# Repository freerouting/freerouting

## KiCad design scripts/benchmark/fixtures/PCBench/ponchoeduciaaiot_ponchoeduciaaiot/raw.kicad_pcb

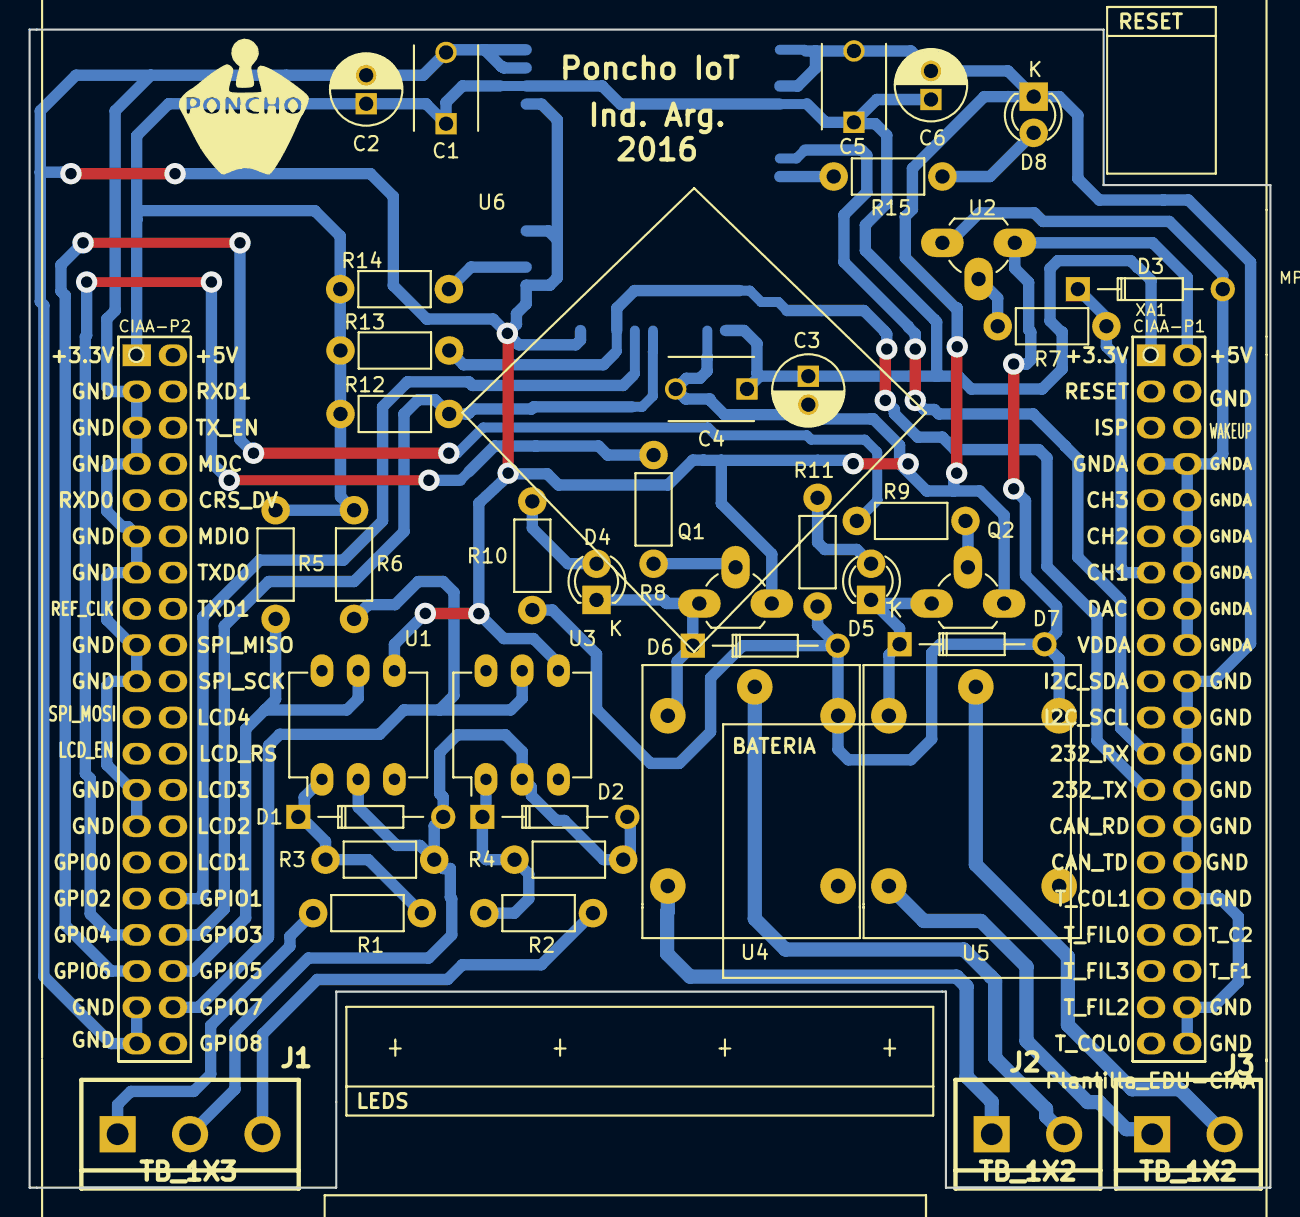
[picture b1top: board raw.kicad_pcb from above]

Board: 2 copper layers, 87.0 x 81.2 mm, 42 parts (0 on the bottom side), 32 nets.

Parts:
C1, C4, C5: 100nF; C_Disc_D6_P5
C2, C3, C6: 2.2uF; C_Radial_D5_L11_P2
D1, D2, D6, D7: 1N4007; Diode_DO-35_SOD27_Horizontal_RM10
D3: 1N4728A; Diode_DO-35_SOD27_Horizontal_RM10
D4, D5, D8: LED; LED-3MM
J1: TB_1X3; bornier3
J2, J3: TB_1X2; bornier2
MP?: Plantilla_EDU-CIAA
Q1, Q2: BC548; TO-92_Rugged
R1, R2: 3.3k; Resistor_Horizontal_RM7mm
R3, R4: 4.7k; Resistor_Horizontal_RM7mm
R5, R6, R8, R9, R12, R14: 10k; Resistor_Horizontal_RM7mm
R7, R15: 150; Resistor_Horizontal_RM7mm
R10, R11: 330; Resistor_Horizontal_RM7mm
R13: 100k; Resistor_Horizontal_RM7mm
U1, U3: 4N25; DIP-6_W7.62mm_LongPads
U2: LM35; TO-92_Rugged
U4, U5: RELAY; Relay5vSI
U6: RN1810E; RN1810
XA1: Conn_Poncho2P_2x_20x2; Conn_Poncho_Mediano

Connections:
+3V3: C1.1, C2.1, C3.1, C4.1, C5.1, C6.1, R5.1, R6.1, R12.1, R13.1, R14.1, U6.4, U6.15, U6.35, XA1.1, XA1.41
+5V: D6.2, D7.2, R10.1, R11.1, U2.1, U4.2, U5.2, XA1.2
/ConectoresPoncho/ANALOG_IN: D3.1, R7.1, XA1.13
/ConectoresPoncho/MODULE_RESET: R12.2, U6.19, XA1.74
/ConectoresPoncho/RXD_EDUCIAA: U6.7, XA1.23
/ConectoresPoncho/TXD_EDUCIAA: R13.2, U6.21, XA1.25
/comm/CMD_CTRL: U6.20, XA1.72
/gpios/IN0: R5.2, U1.5, XA1.76
/gpios/IN1: R6.2, U3.5, XA1.78
/gpios/OUT0: R8.2, XA1.73
/gpios/OUT1: R9.2, XA1.75
GND: C1.2, C2.2, C3.2, C4.2, C5.2, C6.2, D8.1, Q1.3, Q2.3, U1.4, U3.4, U6.1, U6.3, U6.16, U6.23, U6.24, U6.27, U6.34, U6.36, U6.37, XA1.20, XA1.22, XA1.24, XA1.26, XA1.28, XA1.30, XA1.32, XA1.38, XA1.40, XA1.43, XA1.45, XA1.47, XA1.51, XA1.53, XA1.57, XA1.59, XA1.65, XA1.67, XA1.77, XA1.79
GNDA: D3.2, U2.3, XA1.7, XA1.8, XA1.10, XA1.12, XA1.14, XA1.16, XA1.18
unnamed: D1.1, R1.1, R3.1, U1.1
unnamed: D1.2, D2.2, J1.2, R3.2, R4.2, U1.2, U3.2
unnamed: D2.1, R2.1, R4.1, U3.1
unnamed: D4.1, D6.1, Q1.1, U4.1
unnamed: D4.2, R10.2
unnamed: D5.1, D7.1, Q2.1, U5.1
unnamed: D5.2, R11.2
unnamed: D8.2, R15.1
unnamed: J1.1, R1.2
unnamed: J1.3, R2.2
unnamed: J2.1, U4.4
unnamed: J2.2, U4.3
unnamed: J3.1, U5.4
unnamed: J3.2, U5.3
unnamed: Q1.2, R8.1
unnamed: Q2.2, R9.1
unnamed: R7.2, U2.2
unnamed: R14.2, U6.25
unnamed: R15.2, U6.8

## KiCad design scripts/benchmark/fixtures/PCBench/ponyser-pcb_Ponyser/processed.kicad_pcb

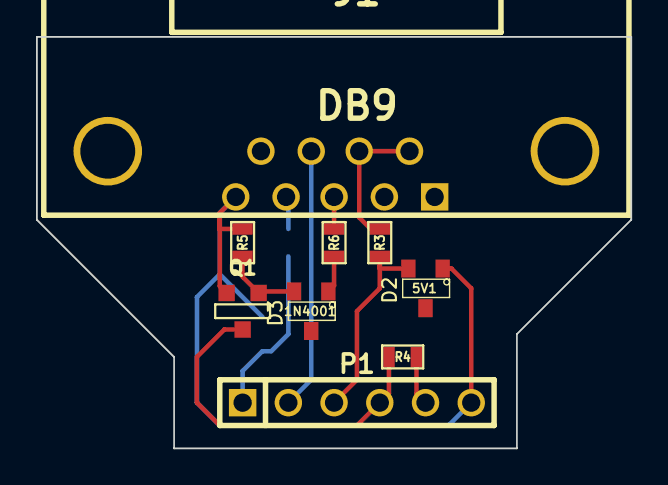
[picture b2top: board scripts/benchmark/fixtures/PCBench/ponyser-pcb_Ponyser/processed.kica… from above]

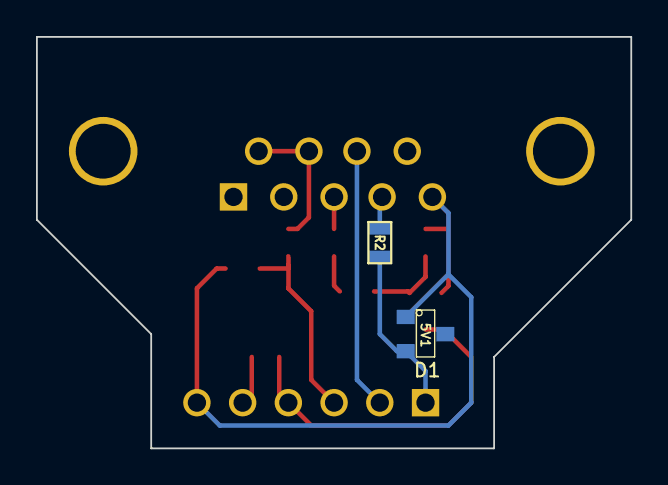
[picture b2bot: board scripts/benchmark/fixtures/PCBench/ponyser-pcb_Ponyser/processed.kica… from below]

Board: 2 copper layers, 33.0 x 22.9 mm, 12 parts (2 on the bottom side), 11 nets.

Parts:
D1, D2: 5V1; SOT23
D3: 1N4001; SOT23
J1: DB9; DB9MC
P1: CONN_6; PIN_ARRAY-6X1
Q1: NPN; SOT23EBC
R2, R3: 4k7; SM0603
R4, R6: 10k; SM0603
R5: 22k; SM0603
STUB: VAL**; STUB

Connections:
GND: D1.1, D2.1, J1.5, P1.6, Q1.1, R5.1
MISO: J1.8, P1.2
MOSI: D1.2, P1.1, R2.2
unnamed: D3.2, Q1.2, R5.2
unnamed: J1.4, R2.1
unnamed: J1.3, R6.1
unnamed: D3.1, R6.2
unnamed: J1.6, J1.7, R3.1
RESET: P1.4, Q1.3, R4.1
SCK: D2.2, P1.3, R3.2
VCC: P1.5, R4.2

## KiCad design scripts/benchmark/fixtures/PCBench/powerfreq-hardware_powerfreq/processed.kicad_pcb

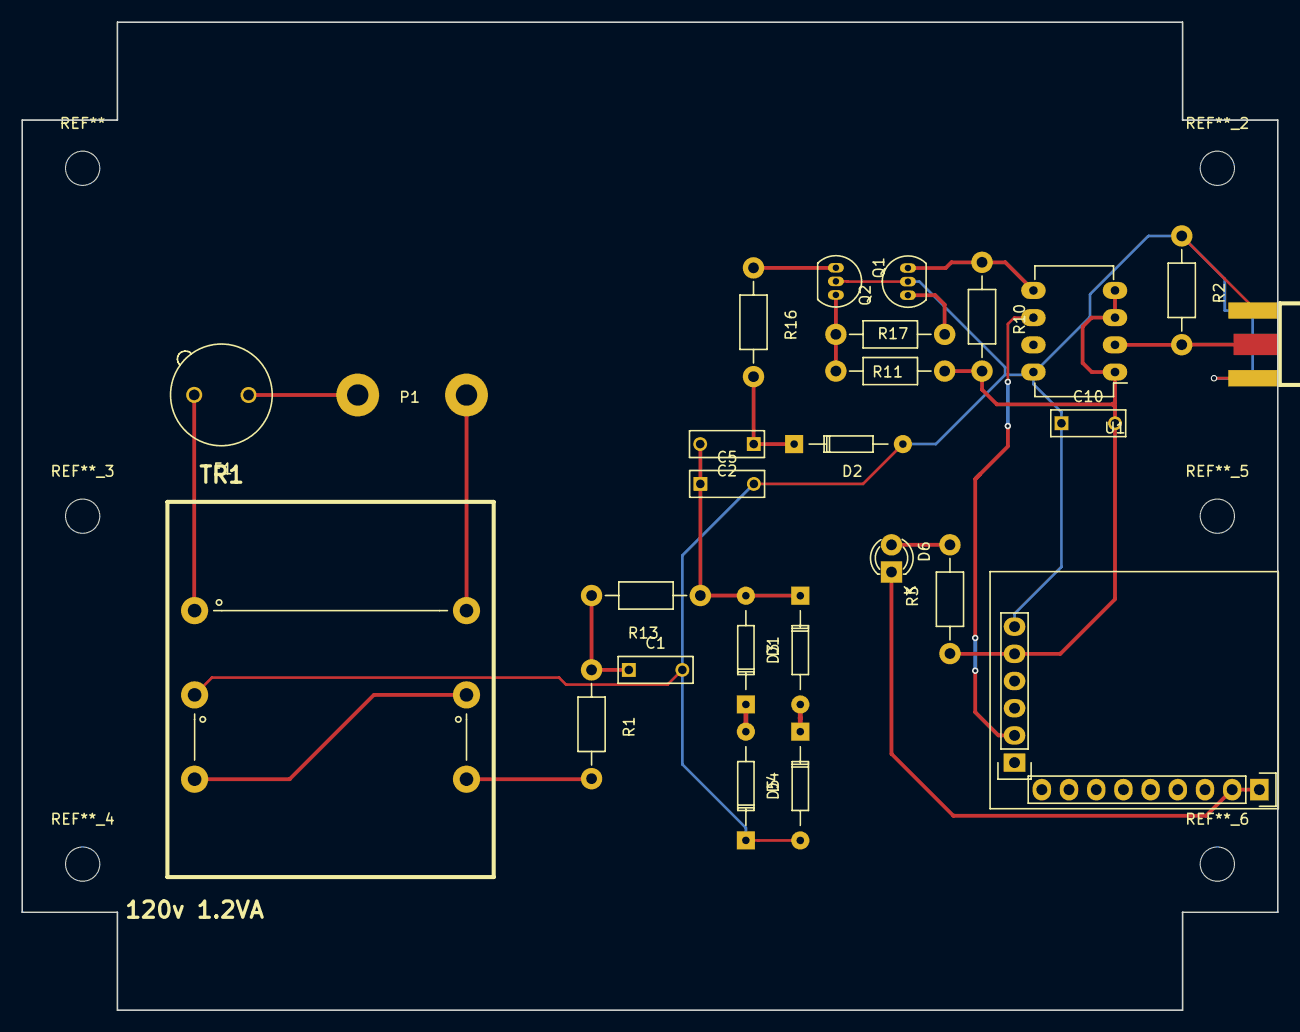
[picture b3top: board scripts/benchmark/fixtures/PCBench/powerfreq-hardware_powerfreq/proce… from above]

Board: 2 copper layers, 117.3 x 92.3 mm, 26 parts (0 on the bottom side), 20 nets.

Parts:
C1, C10: 100nF; C_Rect_L7_W2.5_P5
C2, C5: 10nF; C_Rect_L7_W2.5_P5
D1, D2, D3, D4, D5: 1N4148; Diode_DO-35_SOD27_Horizontal_RM10
D6: LED; LED-3MM
F1: 50mA; Fuseholder_Fuse_TR5_Littlefuse-No560_No460
J1: SMA; SMA_EDGE
P1: CONN_01X03; WireConnection_2.00mmDrill
Q1, Q2: 2N3904; TO-92_Inline_Narrow_Oval
R1: 2k 1W; Resistor_Horizontal_RM10mm
R2: 51; Resistor_Horizontal_RM10mm
R3, R10, R16: 1k; Resistor_Horizontal_RM10mm
R11: 2.2k; Resistor_Horizontal_RM10mm
R13: 20k 2W; Resistor_Horizontal_RM10mm
R17: 250; Resistor_Horizontal_RM10mm
TR1: 120v 1.2VA; 161E120
U1: picPET-03; DIP-8_W7.62mm_LongPads
U2: MIKROE-483; mikroe-483

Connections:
10MHz: J1.1, R2.2, U1.2
60PPS: Q2.3, R10.1, U1.5
+3V3: C10.2, R3.1, R10.2, R17.2, U1.1, U1.3, U1.4, U2.2-5
CLAMP: C2.2, C5.1, D1.2, D3.1, R13.1
GND: C1.2, C5.2, C10.1, D2.2, D4.1, D5.2, J1.0, J1.2, Q1.2, Q2.2, R2.1, TR1.3, U1.8, U2.2-6
unnamed: C1.1, R1.1, R13.2
unnamed: C2.1, D2.1, R16.2
unnamed: D1.1, D4.2
unnamed: D3.2, D5.1
unnamed: D6.1, U2.3-1, U2.3-2
unnamed: D6.2, R3.2
unnamed: F1.1, P1.1
unnamed: F1.2, TR1.1
unnamed: P1.2, TR1.2
unnamed: Q1.1, R16.1
unnamed: Q2.1, R11.1
unnamed: R1.2, TR1.6
unnamed: TR1.4, TR1.5
SERIAL_RX: U1.6, U2.2-2
TRIG: Q1.3, R11.2, R17.1

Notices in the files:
scripts/benchmark/fixtures/PCBench/ponchoeduciaaiot_ponchoeduciaaiot/raw.kicad_pcb:
License: GPL3
